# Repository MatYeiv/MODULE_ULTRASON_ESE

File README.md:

# MODULE_ULTRASON_ESE
Vous trouverez ici les fichiers qui nous ont servis à concevoir le module à capteurs ultrasons de la SAE ESE du S2.

Il y a trois dossiers.

Le dossier avec tout les programmes arduino qui nous ont permis d'obtenir le programme fonctionnel final, nommé "prog_final_memoire.ino"

Le dossier de la simulation LTSpice réalisé en amont du câblage afin de prendre connaissance de son comportement.

Le dossier contenant tout le projet KiCad du module ultrason.

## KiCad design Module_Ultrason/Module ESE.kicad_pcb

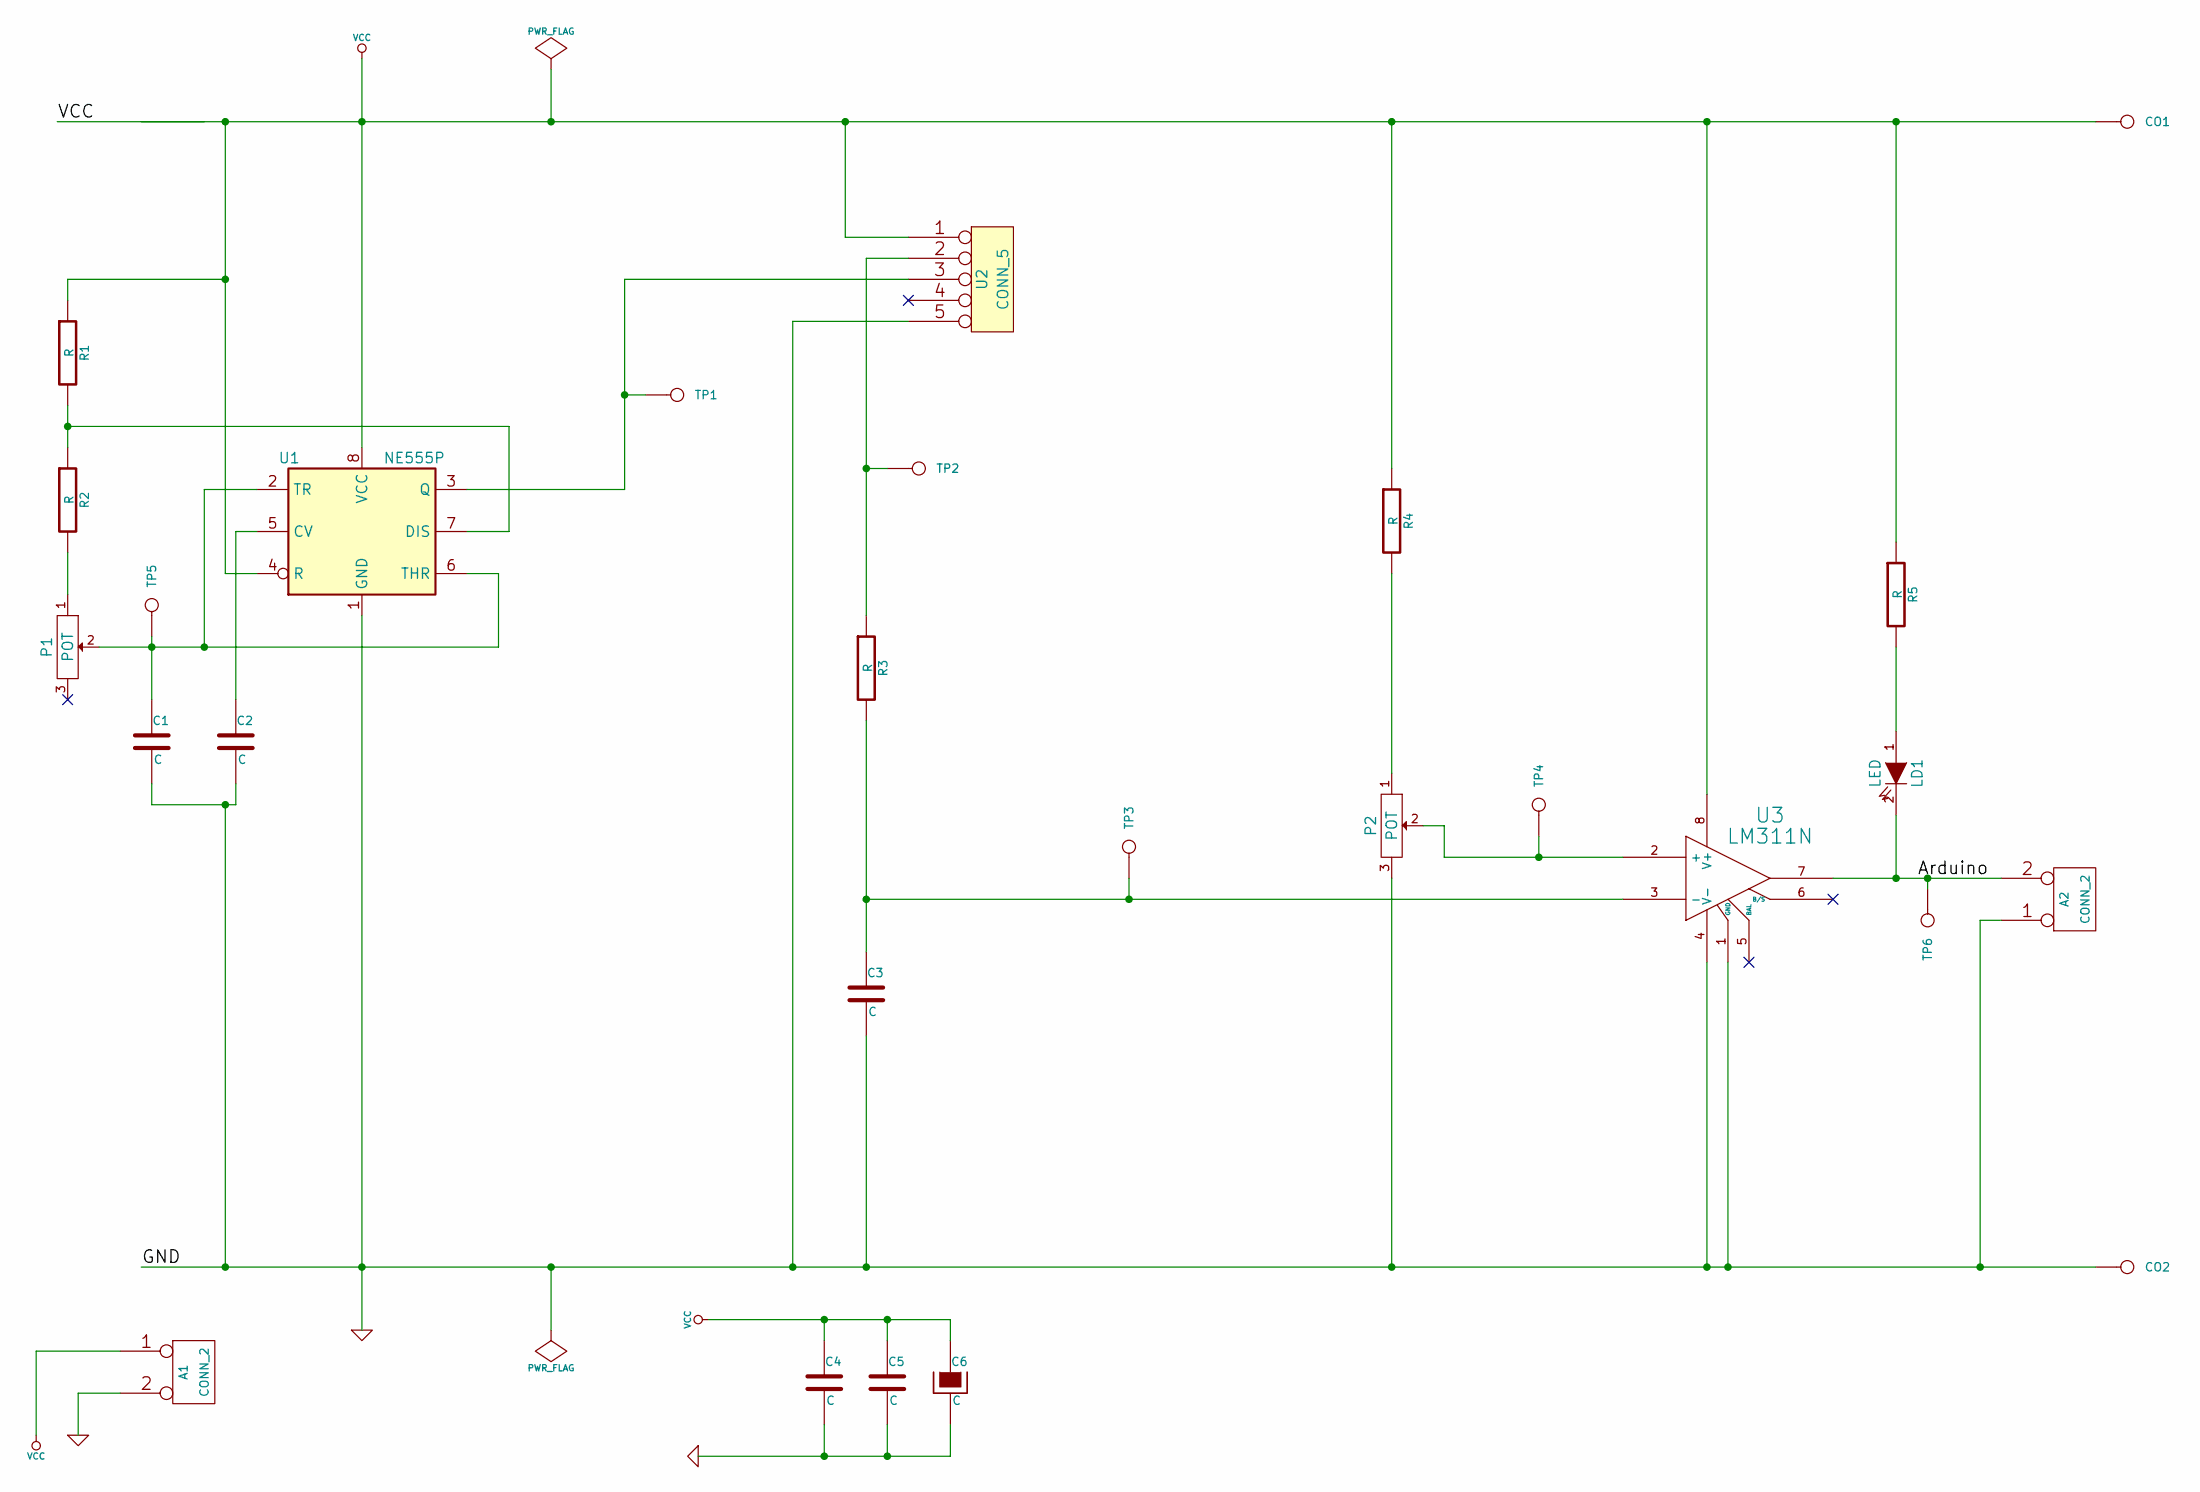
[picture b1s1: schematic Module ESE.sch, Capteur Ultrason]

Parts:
A1, A2: CONN_2
C1, C2, C3, C4, C5, C6: C
CO1, CO2: CONN_1
LD1: LED
P1, P2: POT
R1, R2, R3, R4, R5: R
TP1, TP2, TP3, TP4, TP5, TP6: CONN_1
U1: NE555P; DIP-8_W7.62mm
U2: CONN_5
U3: LM311N

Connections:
/Arduino: A2.2 (PM), LD1.2 (K), TP6.1, U3.7
GND: A1.2 (PM), A2.1, C1.2, C2.2, C3.2, C4.2, C5.2, C6.2, CO2.1, P2.3, U1.1 (GND), U2.5, U3.1 (GND), U3.4 (V-)
unnamed: C3.1, R3.2, TP3.1, U3.3 (-)
unnamed: LD1.1 (A), R5.2
unnamed: P2.2, TP4.1, U3.2 (+)
unnamed: C2.1, U1.5 (CV)
unnamed: P2.1, R4.2
unnamed: C1.1, P1.2, TP5.1, U1.2 (TR), U1.6 (THR)
unnamed: R3.1, TP2.1, U2.2
unnamed: P1.1, R2.2
unnamed: TP1.1, U1.3 (Q), U2.3
unnamed: R1.2, R2.1, U1.7 (DIS)
VCC: A1.1, C4.1, C5.1, C6.1, CO1.1, R1.1, R4.1, R5.1, U1.4 (R), U1.8 (VCC), U2.1, U3.8 (V+)

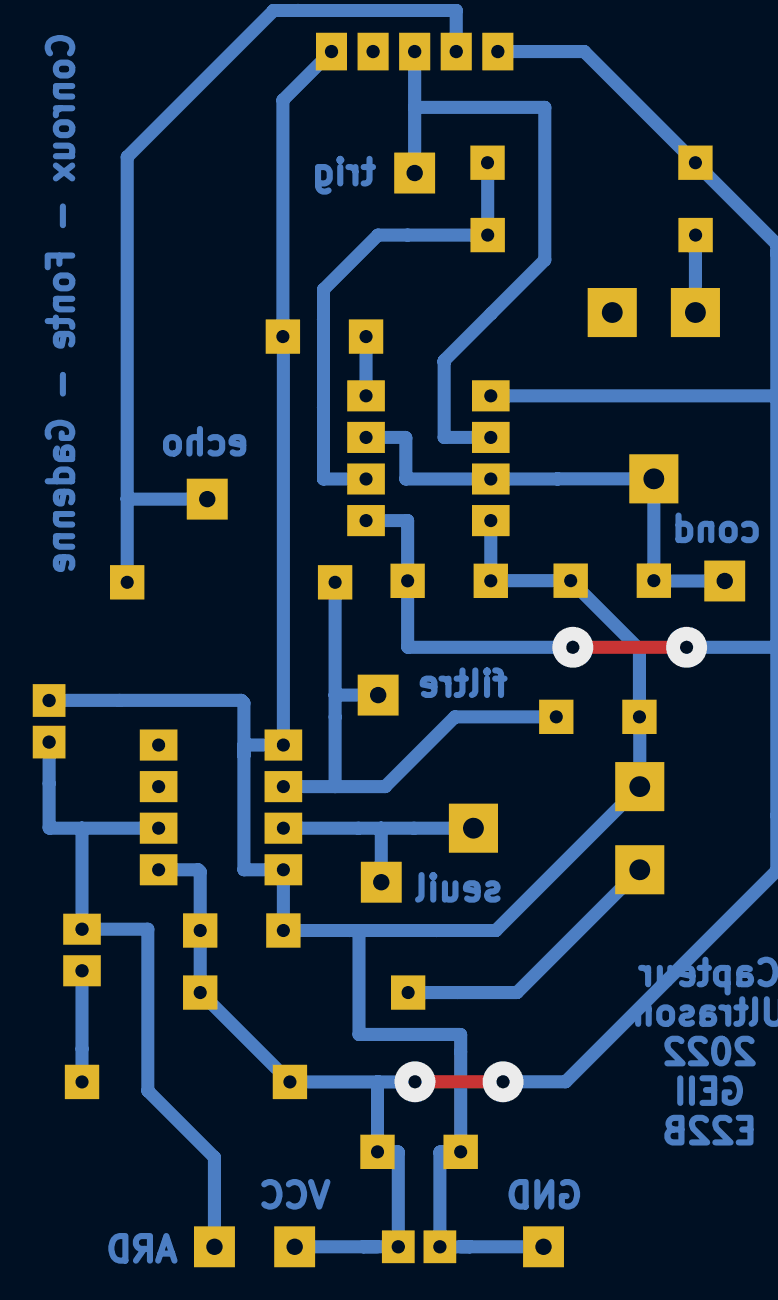
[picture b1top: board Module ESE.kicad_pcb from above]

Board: 2 copper layers, 27 parts (0 on the bottom side), 13 nets.

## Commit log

2022-03-13 Create Dimensionnement_NE555
